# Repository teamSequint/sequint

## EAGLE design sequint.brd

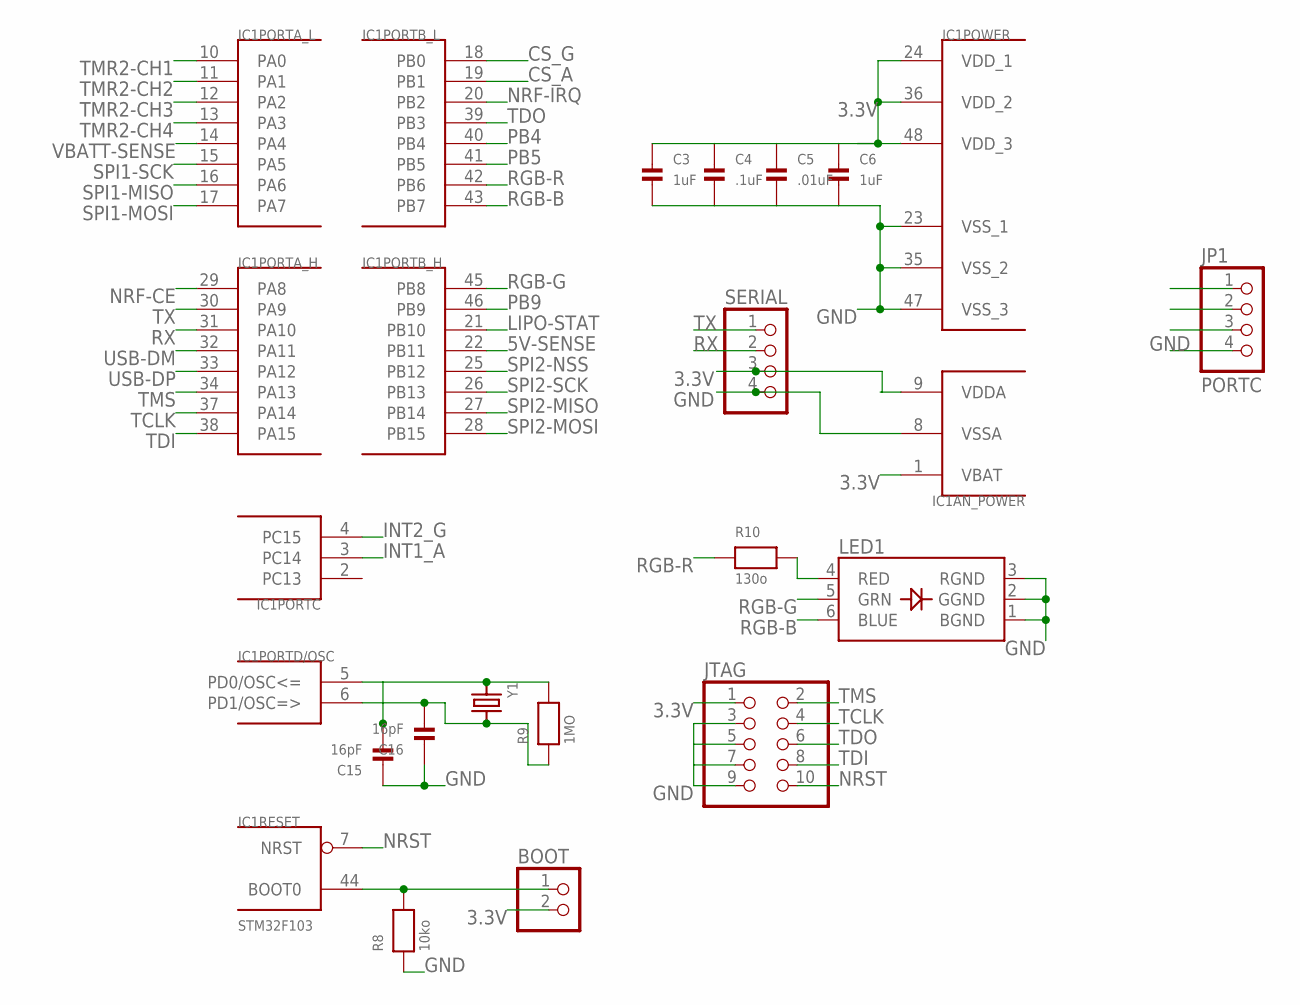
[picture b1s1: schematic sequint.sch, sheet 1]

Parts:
BOOT: HEADER-1X2ROUND; 1X02_ROUND
C3, C6: 1uF; 0402
C4: .1uF; 0402
C5: .01uF; 0402
C15, C16: 16pF; 0402
IC1: STM32F103; TQFP48
JP1: PORTC; 1X04_ROUND
JTAG: HEADER-2X5; 2X05
LED1: LED_RGB_PLCC6CREE-CLV6A; RGBLED_PLCC6
R8: 10ko; 0402
R9: 1MO; 0402
R10: 130o; 0402
SERIAL: HEADER-1X4ROUND; 1X04_ROUND
Y1: CRYSTALSMD; HC49UP

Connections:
3.3V: BOOT.2, C3.1, C4.1, C5.1, C6.1, IC1.1 (VBAT), IC1.9 (VDDA), IC1.24 (VDD_1), IC1.36 (VDD_2), IC1.48 (VDD_3), JTAG.1, SERIAL.3; also elsewhere on the board
5V-SENSE: IC1.22 (PB11); also elsewhere on the board
BOOT0: BOOT.1, IC1.44 (BOOT0), R8.2
CS_A: IC1.19 (PB1); also elsewhere on the board
CS_G: IC1.18 (PB0); also elsewhere on the board
GND: C3.2, C4.2, C5.2, C6.2, C15.1, C16.1, IC1.8 (VSSA), IC1.23 (VSS_1), IC1.35 (VSS_2), IC1.47 (VSS_3), JP1.4, JTAG.3, JTAG.5, JTAG.7, JTAG.9, LED1.1 (BGND), LED1.2 (GGND), LED1.3 (RGND), R8.1, SERIAL.4; also elsewhere on the board
INT1_A: IC1.3 (PC14); also elsewhere on the board
INT2_G: IC1.4 (PC15); also elsewhere on the board
LIPO-STAT: IC1.21 (PB10); also elsewhere on the board
NRF-CE: IC1.29 (PA8); also elsewhere on the board
NRF-IRQ: IC1.20 (PB2); also elsewhere on the board
NRST: IC1.7 (NRST), JTAG.10
PB4: IC1.40 (PB4), JP1.1
PB5: IC1.41 (PB5), JP1.2
PB9: IC1.46 (PB9), JP1.3
PD0: C15.2, IC1.5 (PD0/OSC<=), R9.2, Y1.1
PD1: C16.2, IC1.6 (PD1/OSC=>), R9.1, Y1.2
RGB-B: IC1.43 (PB7), LED1.6 (BLUE)
RGB-G: IC1.45 (PB8), LED1.5 (GRN)
RGB-R: IC1.42 (PB6), R10.1
RGB-RP: LED1.4 (RED), R10.2
RX: IC1.31 (PA10), SERIAL.2
SPI1-MISO: IC1.16 (PA6); also elsewhere on the board
SPI1-MOSI: IC1.17 (PA7); also elsewhere on the board
SPI1-SCK: IC1.15 (PA5); also elsewhere on the board
SPI2-MISO: IC1.27 (PB14); also elsewhere on the board
SPI2-MOSI: IC1.28 (PB15); also elsewhere on the board
SPI2-NSS: IC1.25 (PB12); also elsewhere on the board
SPI2-SCK: IC1.26 (PB13); also elsewhere on the board
TCLK: IC1.37 (PA14), JTAG.4
TDI: IC1.38 (PA15), JTAG.8
TDO: IC1.39 (PB3), JTAG.6
TMR2-CH1: IC1.10 (PA0); also elsewhere on the board
TMR2-CH2: IC1.11 (PA1); also elsewhere on the board
TMR2-CH3: IC1.12 (PA2); also elsewhere on the board
TMR2-CH4: IC1.13 (PA3); also elsewhere on the board
TMS: IC1.34 (PA13), JTAG.2
TX: IC1.30 (PA9), SERIAL.1
USB-DM: IC1.32 (PA11); also elsewhere on the board
USB-DP: IC1.33 (PA12); also elsewhere on the board
VBATT-SENSE: IC1.14 (PA4); also elsewhere on the board

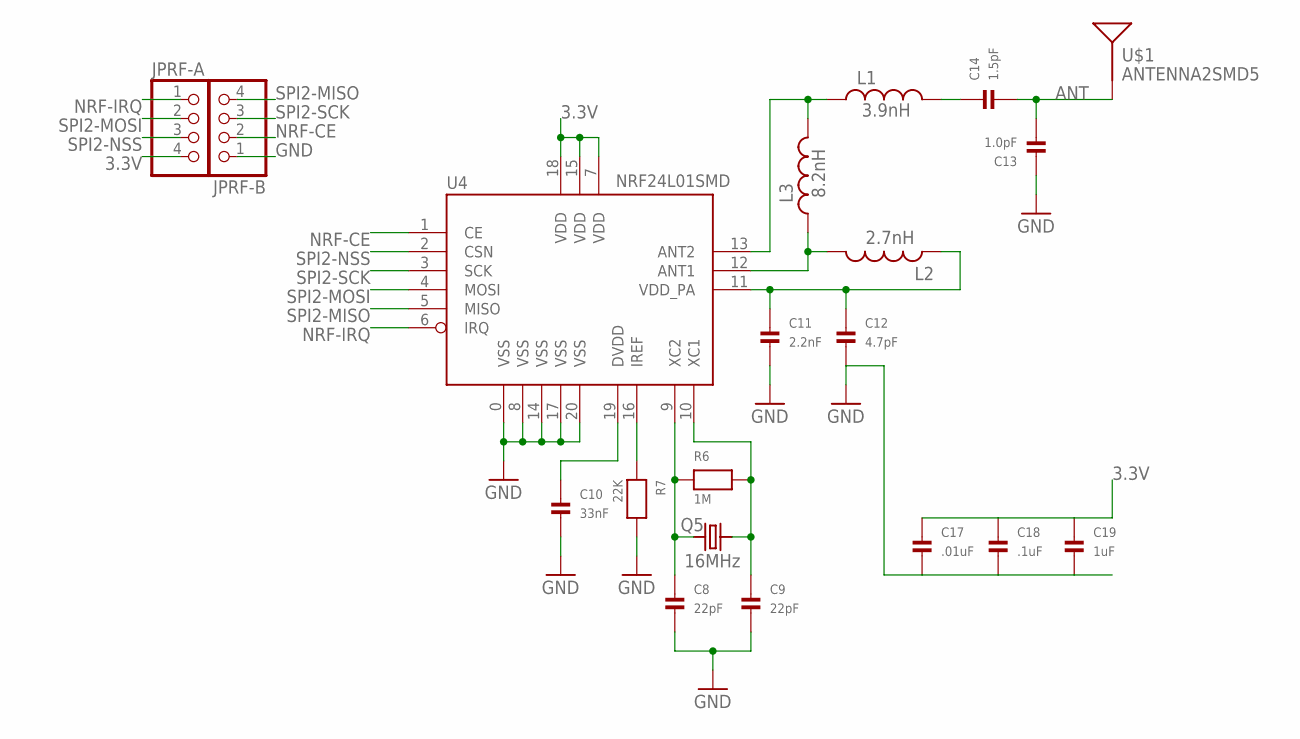
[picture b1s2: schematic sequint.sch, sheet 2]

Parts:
C8, C9: 22pF; 0402
C10: 33nF; 0402
C11: 2.2nF; 0402
C12: 4.7pF; 0402
C13: 1.0pF; 0402
C14: 1.5pF; 0402
C17: .01uF; 0402
C18: .1uF; 0402
C19: 1uF; 0402
JPRF-A: HEADER-1X4ROUND; 1X04_ROUND
JPRF-B: HEADER-1X4ROUND; 1X04_ROUND
L1: 3.9nH; C0402
L2: 2.7nH; C0402
L3: 8.2nH; C0402
Q5: 16MHz; HC49UP
R6: 1M; 0402
R7: 22K; 0402
U4: NRF24L01SMD; QFN20
U$1: ANTENNA2SMD5; ANTENNA-CHIP5

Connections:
3.3V: C17.1, C18.1, C19.1, JPRF-A.4, U4.7 (VDD), U4.15 (VDD), U4.18 (VDD); also elsewhere on the board
ANT: C13.2, C14.2, U$1.FEED
ANT1: L2.2, L3.1, U4.12 (ANT1)
ANT2: L1.1, L3.2, U4.13 (ANT2)
DVDD: C10.1, U4.19 (DVDD)
GND: C8.2, C9.2, C10.2, C11.2, C12.2, C13.1, C17.2, C18.2, C19.2, JPRF-B.1, R7.2, U4.0 (VSS), U4.8 (VSS), U4.14 (VSS), U4.17 (VSS), U4.20 (VSS); also elsewhere on the board
unnamed: C8.1, Q5.1, R6.1, U4.9 (XC2)
unnamed: C9.1, Q5.2, R6.2, U4.10 (XC1)
unnamed: R7.1, U4.16 (IREF)
unnamed: C14.1, L1.2
NRF-CE: JPRF-B.2, U4.1 (CE); also elsewhere on the board
NRF-IRQ: JPRF-A.1, U4.6 (IRQ); also elsewhere on the board
SPI2-MISO: JPRF-B.4, U4.5 (MISO); also elsewhere on the board
SPI2-MOSI: JPRF-A.2, U4.4 (MOSI); also elsewhere on the board
SPI2-NSS: JPRF-A.3, U4.2 (CSN); also elsewhere on the board
SPI2-SCK: JPRF-B.3, U4.3 (SCK); also elsewhere on the board
VDD_PA: C11.1, C12.1, L2.1, U4.11 (VDD_PA)

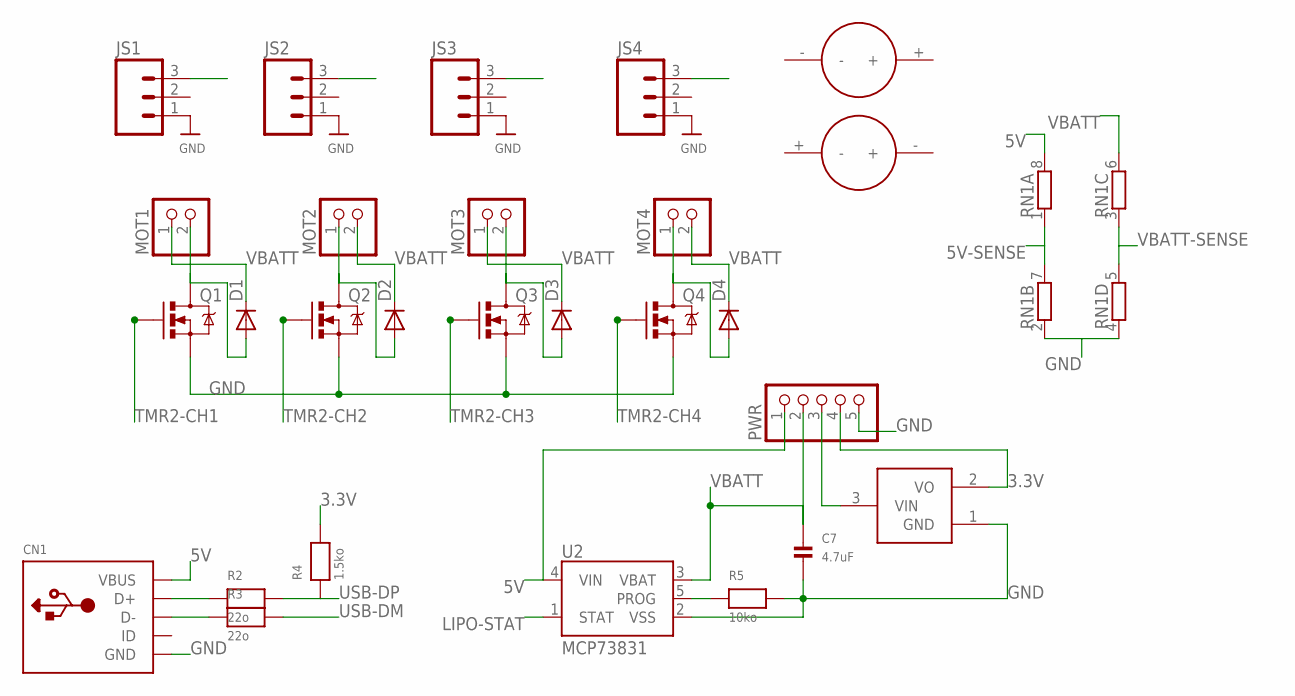
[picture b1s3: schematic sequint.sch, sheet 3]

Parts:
3.3VREG: VREG; SOT23-3
C7: 4.7uF; 0603
CN1: USBMINIB; USB-MINIB
D1, D2, D3, D4: DIODESOD523; SOD523
JS1, JS2, JS3, JS4: M03LOCK; 1X03_LOCK
MOT1, MOT2, MOT3, MOT4: HEADER-1X2ROUND; 1X02_ROUND
PWR: HEADER-1X5ROUND; 1X05_ROUND
Q1, Q2, Q3, Q4: MOSFET-N; SOT23-3
R2, R3: 22o; 0402
R4: 1.5ko; 0402
R5: 10ko; 0402
RN1: RNETWORK; RN8P-4R-CRA06S
U2: MCP73831; SOT23-5
U$6: MOT_RICCW; MOT_RIC_BM_CW
U$7: MOT_RICCCW; MOT_RIC_BM_CCW

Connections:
3.3V: 3.3VREG.2 (VO), PWR.4, R4.2; also elsewhere on the board
5V: CN1.VBUS, PWR.1, RN1.8 (2), U2.4 (VIN)
5V-SENSE: RN1.1, RN1.7 (2); also elsewhere on the board
GND: 3.3VREG.1 (GND), C7.2, CN1.GND, JS1.1, JS2.1, JS3.1, JS4.1, PWR.5, Q1.2 (S), Q2.2 (S), Q3.2 (S), Q4.2 (S), R5.2, RN1.2 (1), RN1.4 (1), U2.2 (VSS); also elsewhere on the board
LIPO-STAT: U2.1 (STAT); also elsewhere on the board
PROG: R5.1, U2.5 (PROG)
TMR2-CH1: JS1.3, Q1.1 (G); also elsewhere on the board
TMR2-CH2: JS2.3, Q2.1 (G); also elsewhere on the board
TMR2-CH3: JS3.3, Q3.1 (G); also elsewhere on the board
TMR2-CH4: JS4.3, Q4.1 (G); also elsewhere on the board
USB+: CN1.D+, R2.1
USB-: CN1.D-, R3.1
USB-DM: R3.2; also elsewhere on the board
USB-DP: R2.2, R4.1; also elsewhere on the board
VBATT: C7.1, D1.C, D2.C, D3.C, D4.C, MOT1.1, MOT2.2, MOT3.1, MOT4.2, PWR.2, RN1.6 (2), U2.3 (VBAT)
VBATT-SENSE: RN1.3 (1), RN1.5 (2); also elsewhere on the board
VIN_3.3V: 3.3VREG.3 (VIN), PWR.3
VL-1: D1.A, MOT1.2, Q1.3 (D)
VL-2: D2.A, MOT2.1, Q2.3 (D)
VL-3: D3.A, MOT3.2, Q3.3 (D)
VL-4: D4.A, MOT4.1, Q4.3 (D)

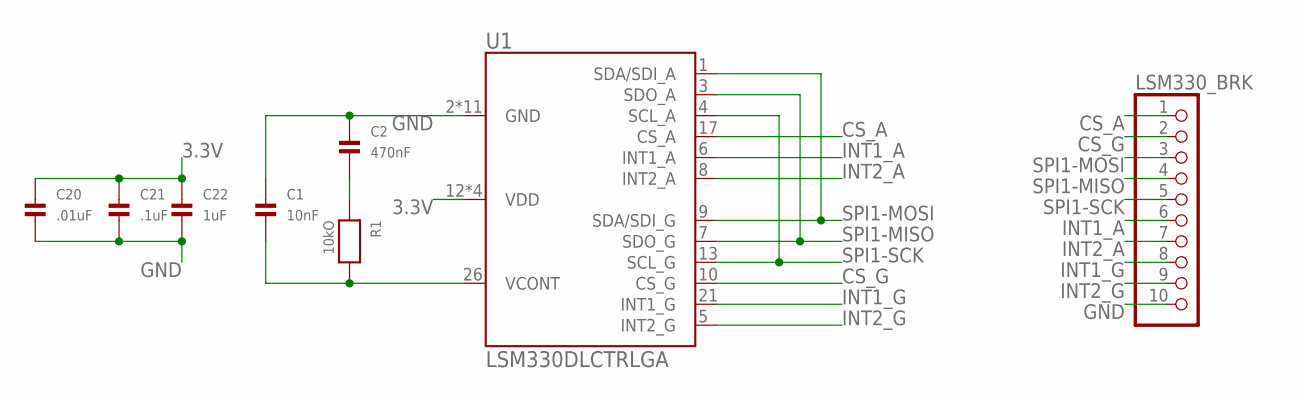
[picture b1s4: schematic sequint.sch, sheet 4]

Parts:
C1: 10nF; 0402
C2: 470nF; 0402
C20: .01uF; 0402
C21: .1uF; 0402
C22: 1uF; 0402
LSM330_BRK: HEADER-1X10ROUND; 1X10_ROUND
R1: 10kO; 0402
U1: LSM330DLCTRLGA; LGA28L

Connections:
3.3V: C20.1, C21.1, C22.1, U1.12 (VDD), U1.15 (VDD), U1.22 (VDD), U1.28 (VDD); also elsewhere on the board
CS_A: LSM330_BRK.1, U1.17 (CS_A); also elsewhere on the board
CS_G: LSM330_BRK.2, U1.10 (CS_G); also elsewhere on the board
GND: C1.1, C2.1, C20.2, C21.2, C22.2, LSM330_BRK.10, U1.2 (GND), U1.11 (GND), U1.14 (GND), U1.16 (GND), U1.18 (GND), U1.19 (GND), U1.20 (GND), U1.23 (GND), U1.24 (GND), U1.25 (GND), U1.27 (GND); also elsewhere on the board
INT1_A: LSM330_BRK.6, U1.6 (INT1_A); also elsewhere on the board
INT1_G: LSM330_BRK.8, U1.21 (INT1_G)
INT2_A: LSM330_BRK.7, U1.8 (INT2_A)
INT2_G: LSM330_BRK.9, U1.5 (INT2_G); also elsewhere on the board
SPI1-MISO: LSM330_BRK.4, U1.3 (SDO_A), U1.7 (SDO_G); also elsewhere on the board
SPI1-MOSI: LSM330_BRK.3, U1.1 (SDA/SDI_A), U1.9 (SDA/SDI_G); also elsewhere on the board
SPI1-SCK: LSM330_BRK.5, U1.4 (SCL_A), U1.13 (SCL_G); also elsewhere on the board
VCONT: C1.2, R1.2, U1.26 (VCONT)
VCONT_1: C2.2, R1.1

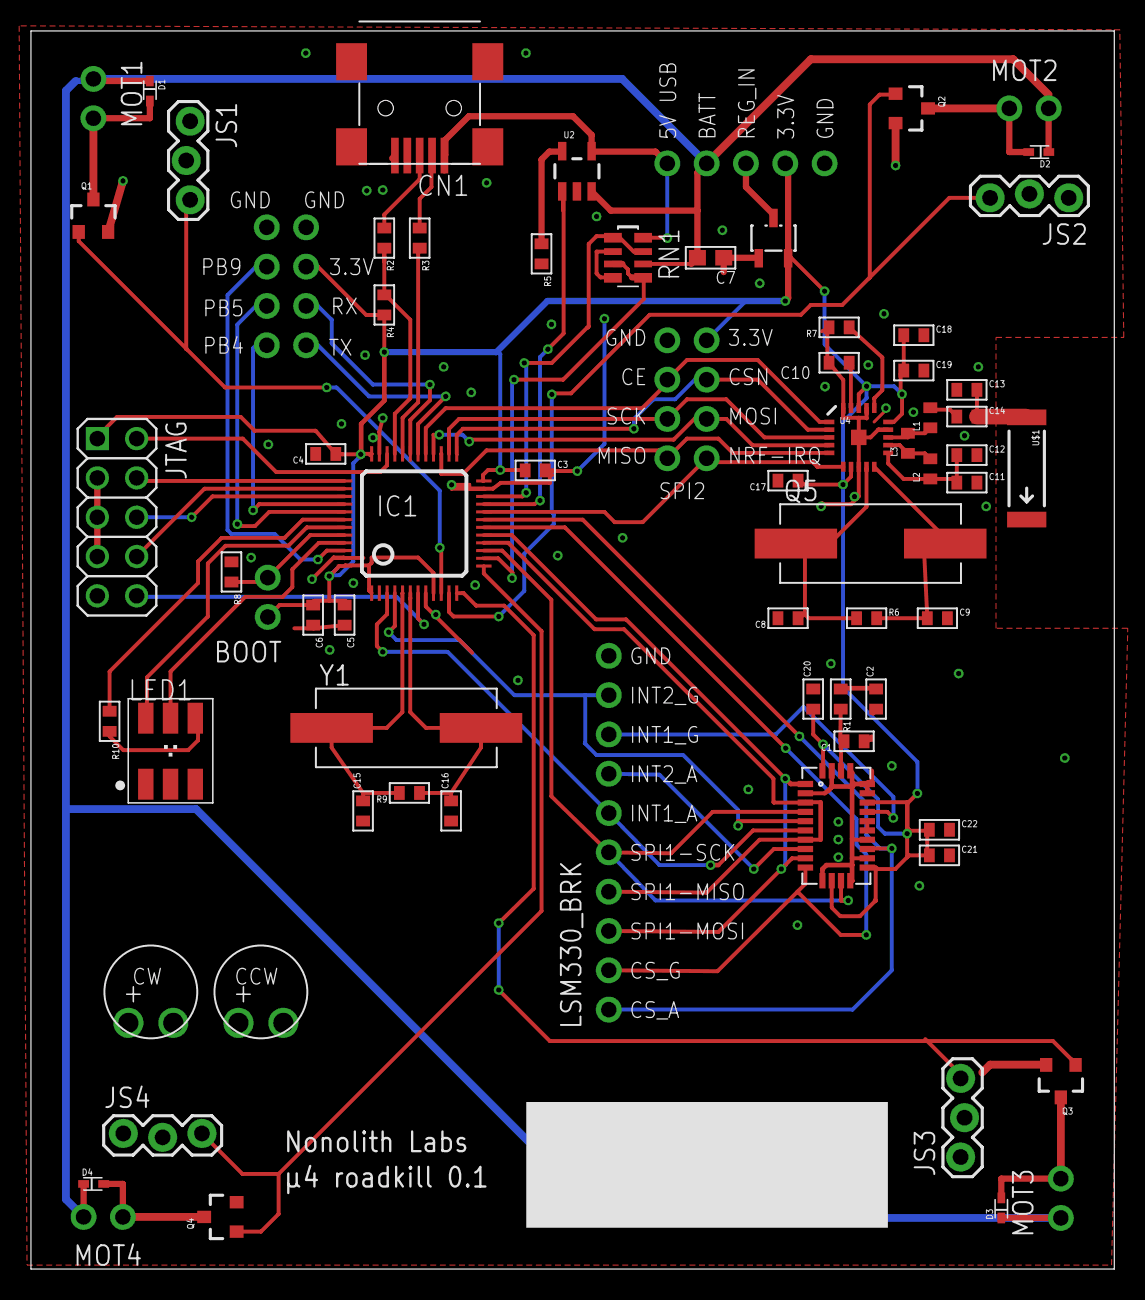
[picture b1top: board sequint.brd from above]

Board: 2 copper layers, 70.0 x 80.0 mm, 72 parts (0 on the bottom side), 64 nets.

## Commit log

2012-03-19 f1rst p0st!
2012-03-20 preliminary component groupings and some routing done on roadkill board. 2 layers.
2012-03-20 fyeahgroundplane and fyeahproperboardsizing
2012-03-20 all sheets routed and roughly placed. sheet-to-sheet connections underway. 2 layers, 16 mil pwr, 12 mil sig.
2012-03-22 Roadkill routed. Fails DRC for reasons that will be easy to fix after a good night's sleep. I isolated the antenna trace...should I? 10 mils min, 2 layer, motors on corners, one heck of a rat's nest.
2012-03-23 Fix routing
2012-03-23 fix airwire
2012-03-23 DRC / cleanup
2012-03-23 More routing tweaks
2012-03-23 Break out portC
2012-03-23 Fix airwires
2012-03-23 Roadkill passes all meaninful DRC (clearance issues around all the fine-pitch ICs). Added silkscreen for name, rev, serial. Logo in copper?
2012-03-26 label header pins
2012-03-28 Some non-power traces were 12mil. Make them 10mil
2012-03-28 Silkscreen
2012-04-02 updated nonolith.lbr
2012-04-03 more DRC fixes
2012-04-03 oops
2012-04-03 s/trace antenna/chip antenna/, passes DRC.
2012-04-04 fix nRF pin names
2012-04-04 removed fatty diodes, s/0603/0402/
2012-04-04 fixed DRC errors
2012-04-04 added snubber diodes in SOD523 aka tiny
2012-04-04 Pack radio tighter. Add GND vias
2012-04-04 Make GND plane cutout rectangular
2012-04-04 Vias around USB
2012-04-06 Add servo headers
2012-04-16 Add test motor footprint
2012-04-16 Fix routing on two STM32 pins; update lbr
2012-04-17 Move nrf-ce to pin 31 for better routing
2012-04-17 rearrange more pins
2012-04-17 Move LED
2012-04-17 Move USART to USART1, which supports bootloader.
2012-04-17 Clean up

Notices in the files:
parts and their libraries:
SparkFun: Licensing: CC v3.0 Share-Alike You are welcome to use this library for commercial purposes.
